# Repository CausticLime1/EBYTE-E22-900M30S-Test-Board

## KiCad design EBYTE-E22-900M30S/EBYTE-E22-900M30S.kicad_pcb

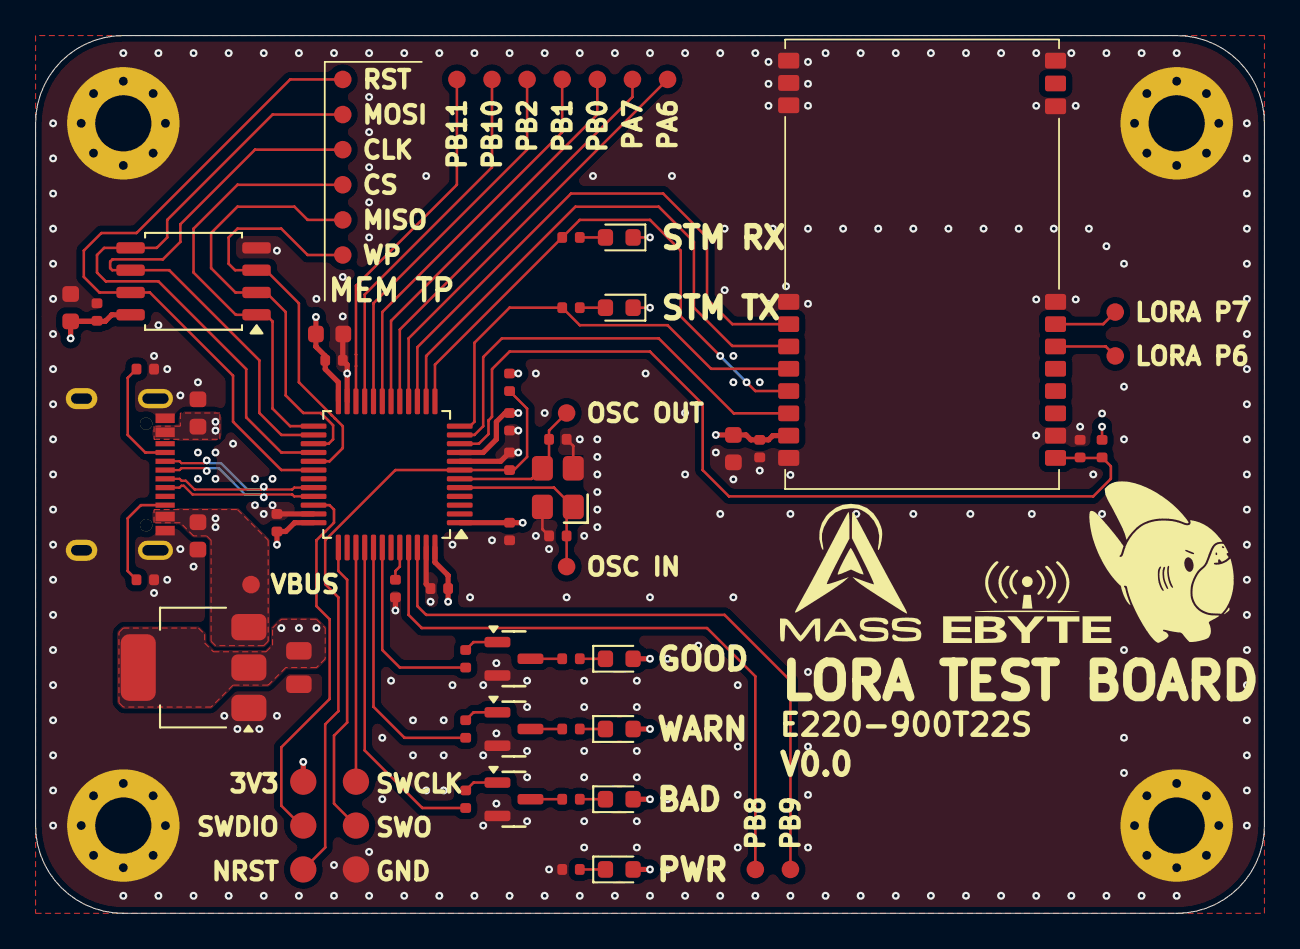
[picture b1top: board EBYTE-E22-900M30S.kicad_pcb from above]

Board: 4 copper layers, 70.0 x 50.0 mm, 71 parts (0 on the bottom side), 52 nets.

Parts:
C1, C3, C4, C5, C6, C7, C8, C10, C17: 100nF; C_0402
C2, C9, C13, C15, C16: 10uF; C_0603
C11, C12: 10pF; C_0402
C14: 22uF; C_0805
D1, D2, D3, D4, D5, D6: LED; LED_0603_1608Metric
H1, H2, H3, H4: MountingHole_Pad; MountingHole_3.2mm_M3_Pad_Via
J1: Conn_01x06_Socket; SWD-POGO_Recpt
Q1, Q2, Q3: S8050; Q_SOT-23
R1, R2, R3, R5, R7, R9: 10K; R_0402
R4, R6, R8, R12: 330R; R_0402
R10, R11: 5.1K; R_0402
R13, R14: 1K; R_0402
TP1, TP2, TP3, TP4, TP5, TP6, TP7, TP8, TP9, TP10, TP11, TP12, TP13, TP14, TP15, TP16, TP17, TP18, TP19, TP20: TestPoint; TestPoint_Pad_D1.0mm
U1: E220-400-900T22S
U2: STM32F103CBTx; LQFP-48_7x7mm_P0.5mm
U3: AMS1117-3.3; SOT-223-3_TabPin2
U4: W25Q128JVS; SOIC-8_5.3x5.3mm_P1.27mm
USB1: TYPE-C 16PIN 2MD(073); USB-C-SMD_TYPE-C-6PIN-2MD-073
X1: X322516MLB4SI; OSC-SMD_4P-L3.2-W2.5-BL

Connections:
+3.3V: C1.1, C2.1, C4.1, C5.1, C6.1, C7.1, C8.1, C9.1, C13.1, C14.1, C17.1, D1.2 (A), D2.2 (A), D3.2 (A), D4.2 (A), J1.1, R1.1, R2.1, U1.25 (VCC), U2.1 (VBAT), U2.9 (VDDA), U2.24 (VDD), U2.36 (VDD), U2.48 (VDD), U3.2 (VO), U4.8 (VCC)
+5V: C15.1, C16.1, TP18.1 (1_1), U3.3 (VI), USB1.2 (VBUS), USB1.11 (VBUS)
/LED1_TIM4_CH1: R5.2, U2.42 (PB6)
/LED2_TIM3_CH2: R7.2, U2.41 (PB5)
/LED3_TIM3_CH1: R9.2, U2.40 (PB4)
/LoRa_AUX: U1.24 (AUX), U2.11 (PA1)
/LoRa_M0: U1.20 (M0), U2.15 (PA5)
/LoRa_M1: U1.21 (M1), U2.14 (PA4)
/LoRa_NRST: C3.1, R1.2, U1.1 (NRST), U2.10 (PA0)
/MEM_CS: TP1.1 (1_1), U2.25 (PB12), U4.1 (~CS)
/MEM_RST: TP6.1 (1_1), U2.30 (PA9), U4.7 (~HOLD/~RESET/IO_{3})
/MEM_WP: TP5.1 (1_1), U2.29 (PA8), U4.3 (~WP/IO_{2})
/OSC_IN: C12.1, TP9.1 (1_1), U2.5 (PD0), X1.1 (OSC)
/OSC_OUT: C11.1, TP10.1 (1_1), U2.6 (PD1), X1.3 (OSC)
/P6: TP7.1 (1_1), U1.6 (PROG)
/P7: TP8.1 (1_1), U1.7 (PROG)
/SPI2_CLK: TP2.1 (1_1), U2.26 (PB13), U4.6 (CLK)
/SPI2_MISO: TP4.1 (1_1), U2.27 (PB14), U4.2 (DO/IO_{1})
/SPI2_MOSI: TP3.1 (1_1), U2.28 (PB15), U4.5 (DI/IO_{0})
/STM_BOOT0: R3.1, U2.44 (BOOT0)
/STM_NRST: C10.1, J1.3, R2.2, U2.7 (NRST)
/SWCLK: J1.5, U2.37 (PA14)
/SWDIO: J1.2, U2.34 (PA13)
/SWO: J1.4, U2.39 (PB3)
/UART2_STM_RX_LoRa_TX: R14.2, U1.23 (TXD), U2.13 (PA3)
/UART2_STM_TX_LoRa_RX: R13.2, U1.22 (RXD), U2.12 (PA2)
/USB_D+: U2.33 (PA12), USB1.6 (DP1), USB1.8 (DP2)
/USB_D-: U2.32 (PA11), USB1.5 (DN2), USB1.7 (DN1)
GND: C1.2, C2.2, C3.2, C4.2, C5.2, C6.2, C7.2, C8.2, C9.2, C10.2, C11.2, C12.2, C13.2, C14.2, C15.2, C16.2, C17.2, D5.1 (K), D6.1 (K), H1.1 (1_1), H2.1 (1_1), H3.1 (1_1), H4.1 (1_1), J1.6, Q1.2 (E), Q2.2 (E), Q3.2 (E), R3.2, R10.2, R11.2, R12.2, U1.2 (GND), U1.8 (GND), U1.11 (GND), U1.13 (GND), U1.14 (GND), U1.15 (GND), U1.16 (GND), U1.19 (GND), U1.26 (GND), U2.8 (VSSA), U2.23 (VSS), U2.35 (VSS), U2.47 (VSS), U3.1 (GND), U4.4 (GND), USB1.1 (GND), USB1.12 (GND), USB1.13 (SHELL), USB1.14 (SHELL), X1.2 (GND), X1.4 (GND)
unnamed: D1.1 (K), R4.1
unnamed: D2.1 (K), R6.1
unnamed: D3.1 (K), R8.1
unnamed: D4.1 (K), R12.1
unnamed: D5.2 (A), R13.1
unnamed: D6.2 (A), R14.1
unnamed: Q1.1 (B), R5.1
unnamed: Q1.3 (C), R4.2
unnamed: Q2.1 (B), R7.1
unnamed: Q2.3 (C), R6.2
unnamed: Q3.1 (B), R9.1
unnamed: Q3.3 (C), R8.2
unnamed: TP11.1 (1_1), U2.16 (PA6)
unnamed: TP12.1 (1_1), U2.17 (PA7)
unnamed: TP17.1 (1_1), U2.18 (PB0)
unnamed: TP16.1 (1_1), U2.19 (PB1)
unnamed: TP15.1 (1_1), U2.20 (PB2)
unnamed: TP20.1 (1_1), U2.45 (PB8)
unnamed: TP19.1 (1_1), U2.46 (PB9)
unnamed: TP14.1 (1_1), U2.21 (PB10)
unnamed: TP13.1 (1_1), U2.22 (PB11)
unnamed: R11.1, USB1.4 (CC1)
unnamed: R10.1, USB1.10 (CC2)

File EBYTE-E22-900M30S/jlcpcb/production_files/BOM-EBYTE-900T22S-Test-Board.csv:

Comment,Designator,Footprint,LCSC,Quantity
S8050,"Q1,Q2,Q3",Q_SOT-23,C364312,3
TYPE-C 16PIN 2MD(073),USB1,USB-C-SMD_TYPE-C-6PIN-2MD-073,C2765186,1
X322516MLB4SI,X1,OSC-SMD_4P-L3.2-W2.5-BL,C13738,1
TestPoint,TP19,TestPoint_Pad_D1.0mm,,1
TestPoint,TP20,TestPoint_Pad_D1.0mm,,1
TestPoint,TP11,TestPoint_Pad_D1.0mm,,1
TestPoint,TP17,TestPoint_Pad_D1.0mm,,1
TestPoint,TP12,TestPoint_Pad_D1.0mm,,1
TestPoint,TP16,TestPoint_Pad_D1.0mm,,1
TestPoint,TP15,TestPoint_Pad_D1.0mm,,1
TestPoint,TP14,TestPoint_Pad_D1.0mm,,1
TestPoint,TP13,TestPoint_Pad_D1.0mm,,1
TestPoint,TP18,TestPoint_Pad_D1.0mm,,1
TestPoint,TP5,TestPoint_Pad_D1.0mm,,1
TestPoint,TP2,TestPoint_Pad_D1.0mm,,1
TestPoint,TP1,TestPoint_Pad_D1.0mm,,1
TestPoint,TP6,TestPoint_Pad_D1.0mm,,1
TestPoint,TP4,TestPoint_Pad_D1.0mm,,1
TestPoint,TP3,TestPoint_Pad_D1.0mm,,1
TestPoint,TP9,TestPoint_Pad_D1.0mm,,1
TestPoint,TP10,TestPoint_Pad_D1.0mm,,1
TestPoint,TP7,TestPoint_Pad_D1.0mm,,1
TestPoint,TP8,TestPoint_Pad_D1.0mm,,1
100nF,C1,C_0402,,1
10uF,C2,C_0603,,1
1K,R14,R_0402,,1
1K,R13,R_0402,,1
LED,D6,LED_0603_1608Metric,,1
LED,D5,LED_0603_1608Metric,,1
W25Q128JVS,U4,SOIC-8_5.3x5.3mm_P1.27mm,,1
100nF,C17,C_0402,,1
10uF,C13,C_0603,,1
Conn_01x06_Socket,J1,SWD-POGO_Recpt,,1
100nF,C4,C_0402,,1
100nF,C7,C_0402,,1
100nF,C3,C_0402,,1
100nF,C5,C_0402,,1
100nF,C6,C_0402,,1
100nF,C8,C_0402,,1
10pF,C11,C_0402,,1
10uF,C9,C_0603,,1
10pF,C12,C_0402,,1
100nF,C10,C_0402,,1
10K,R2,R_0402,,1
330R,R6,R_0402,,1
10K,R3,R_0402,,1
LED,D2,LED_0603_1608Metric,,1
22uF,C14,C_0805,,1
LED,D1,LED_0603_1608Metric,,1
330R,R4,R_0402,,1
LED,D3,LED_0603_1608Metric,,1
10K,R1,R_0402,,1
10K,R5,R_0402,,1
5.1K,R11,R_0402,,1
AMS1117-3.3,U3,SOT-223-3_TabPin2,,1
10K,R7,R_0402,,1
10K,R9,R_0402,,1
5.1K,R10,R_0402,,1
STM32F103CBTx,U2,LQFP-48_7x7mm_P0.5mm,,1
330R,R8,R_0402,,1
LED,D4,LED_0603_1608Metric,,1
330R,R12,R_0402,,1
10uF,C15,C_0603,,1
10uF,C16,C_0603,,1

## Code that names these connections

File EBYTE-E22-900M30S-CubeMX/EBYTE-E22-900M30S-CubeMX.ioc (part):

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Mcu.Name=STM32F103V(C-D-E)Tx
Mcu.Package=LQFP100
Mcu.UserName=STM32F103VCTx
PA11.Mode=Device
PA11.Signal=USB_DM
PA12.Mode=Device
PA12.Signal=USB_DP
PA13.Mode=Serial_Wire
PA13.Signal=SYS_JTMS-SWDIO
PA14.Mode=Serial_Wire
PA14.Signal=SYS_JTCK-SWCLK
PA4.Signal=GPIO_Output
PA5.Mode=Full_Duplex_Master
PA5.Signal=SPI1_SCK
PA6.Mode=Full_Duplex_Master
PA6.Signal=SPI1_MISO
PA7.Mode=Full_Duplex_Master
PA7.Signal=SPI1_MOSI
PB10.Mode=I2C
PB10.Signal=I2C2_SCL
PB11.Mode=I2C
PB11.Signal=I2C2_SDA
PB13.Mode=Full_Duplex_Master
PB13.Signal=SPI2_SCK
PB14.Mode=Full_Duplex_Master
PB14.Signal=SPI2_MISO
PB15.Mode=Full_Duplex_Master
PB15.Signal=SPI2_MOSI
PB3.Mode=Full_Duplex_Master
PB3.Signal=SPI3_SCK
PB4.Mode=Full_Duplex_Master
PB4.Signal=SPI3_MISO
PB5.Mode=Full_Duplex_Master
PB5.Signal=SPI3_MOSI
PB8.Mode=I2C
PB8.Signal=I2C1_SCL
PB9.Mode=I2C
PB9.Signal=I2C1_SDA
PC4.Signal=GPIO_Output
PC5.Signal=GPIO_Output
PD8.Mode=Asynchronous
PD8.Signal=USART3_TX
PD9.Mode=Asynchronous
PD9.Signal=USART3_RX
board=custom
